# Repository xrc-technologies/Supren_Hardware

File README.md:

# Supren_Hardware
Hardware for Supren Radio Controller

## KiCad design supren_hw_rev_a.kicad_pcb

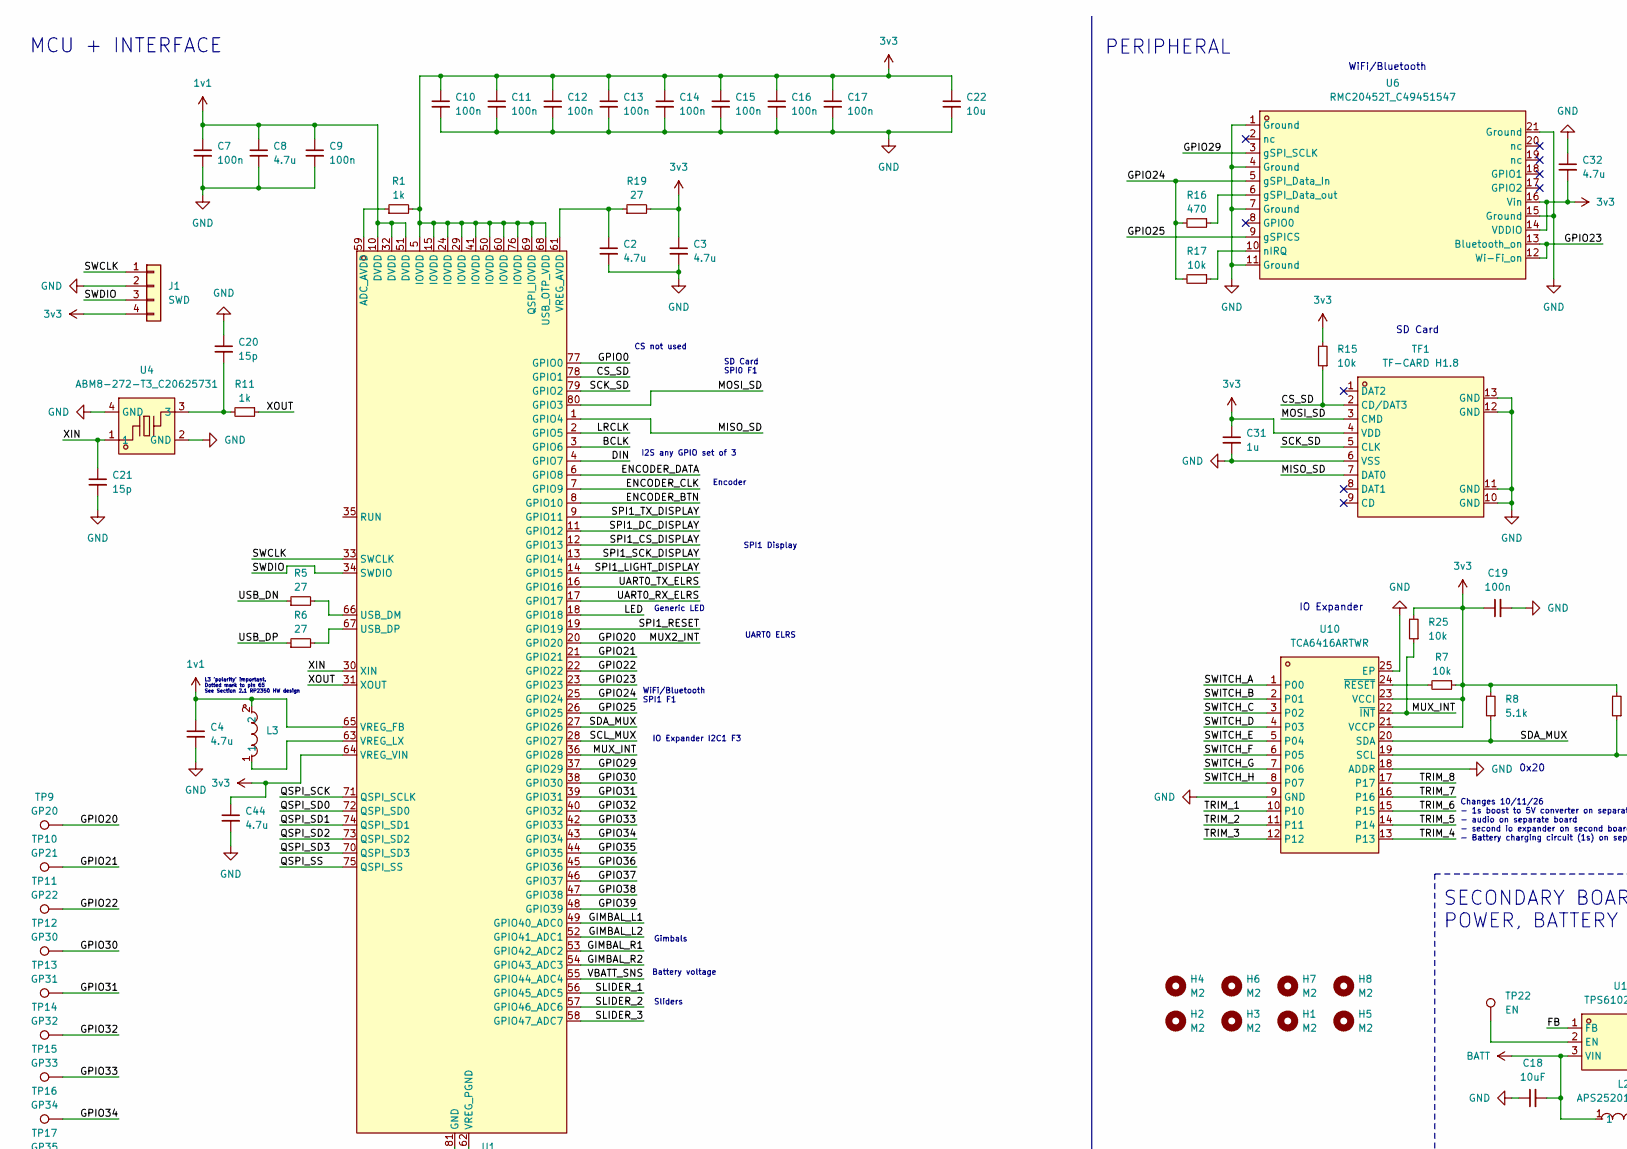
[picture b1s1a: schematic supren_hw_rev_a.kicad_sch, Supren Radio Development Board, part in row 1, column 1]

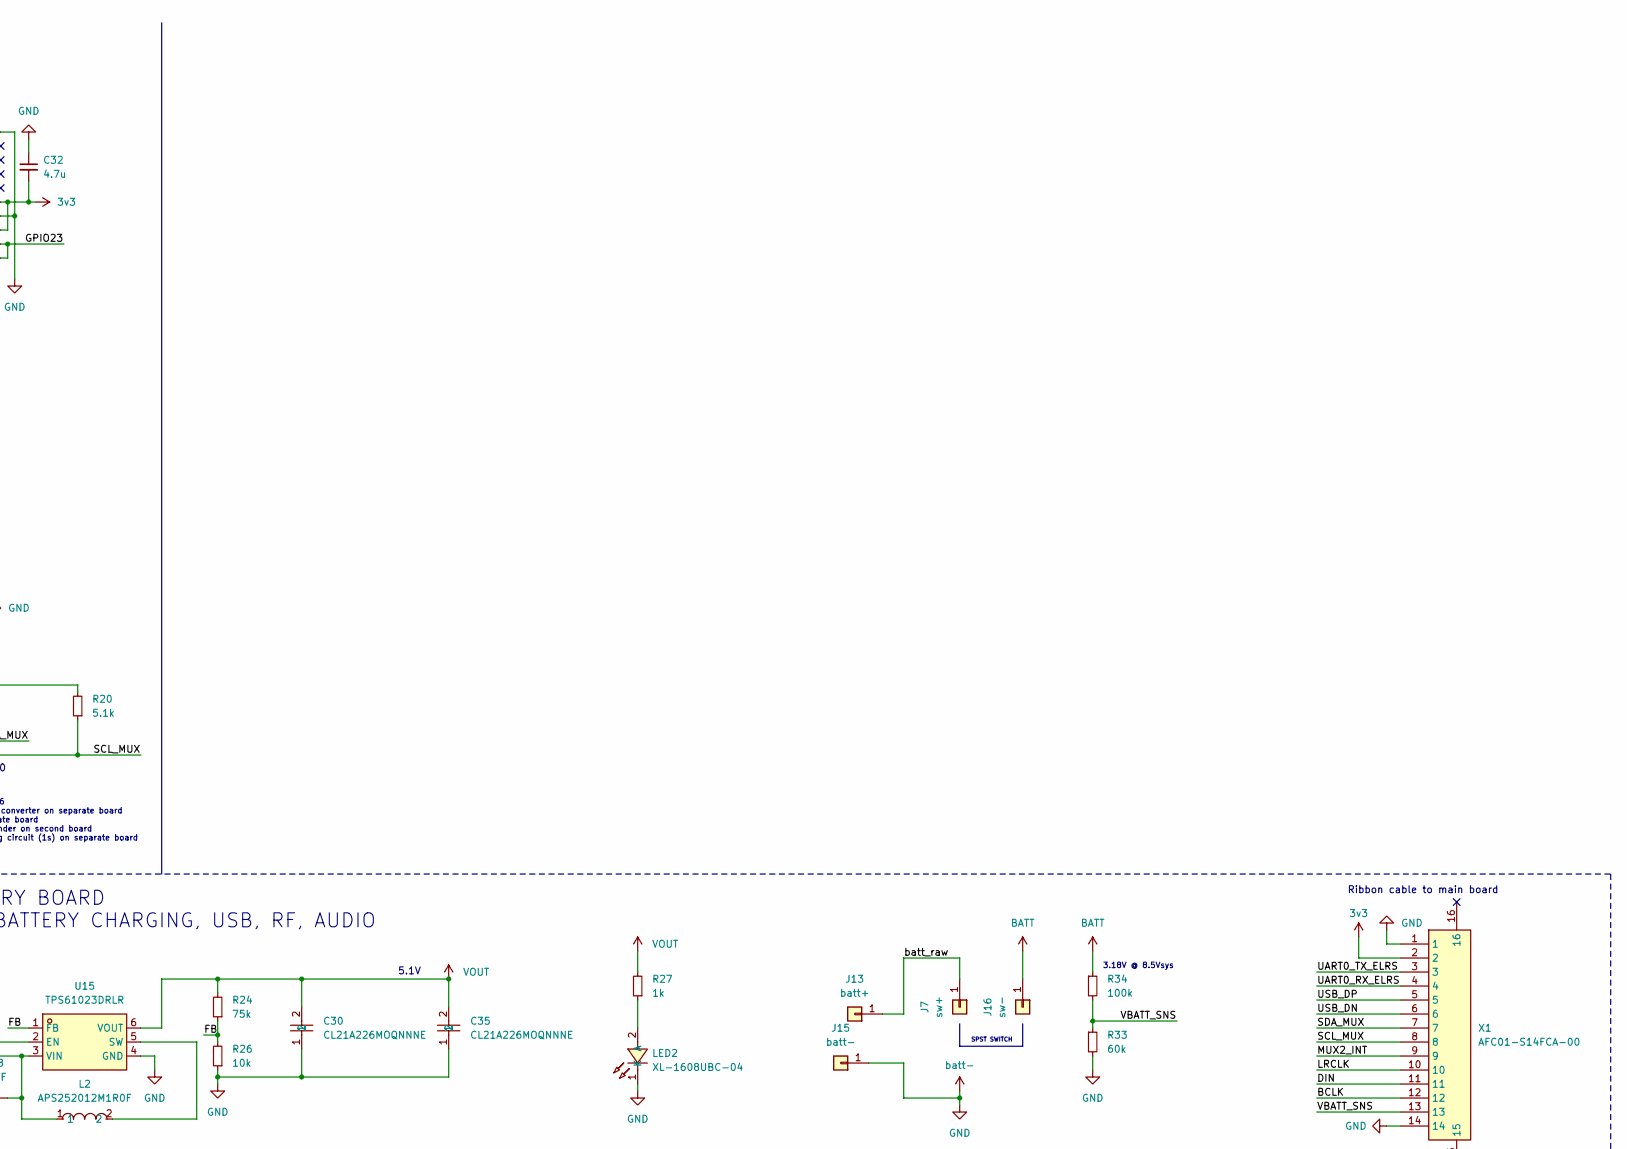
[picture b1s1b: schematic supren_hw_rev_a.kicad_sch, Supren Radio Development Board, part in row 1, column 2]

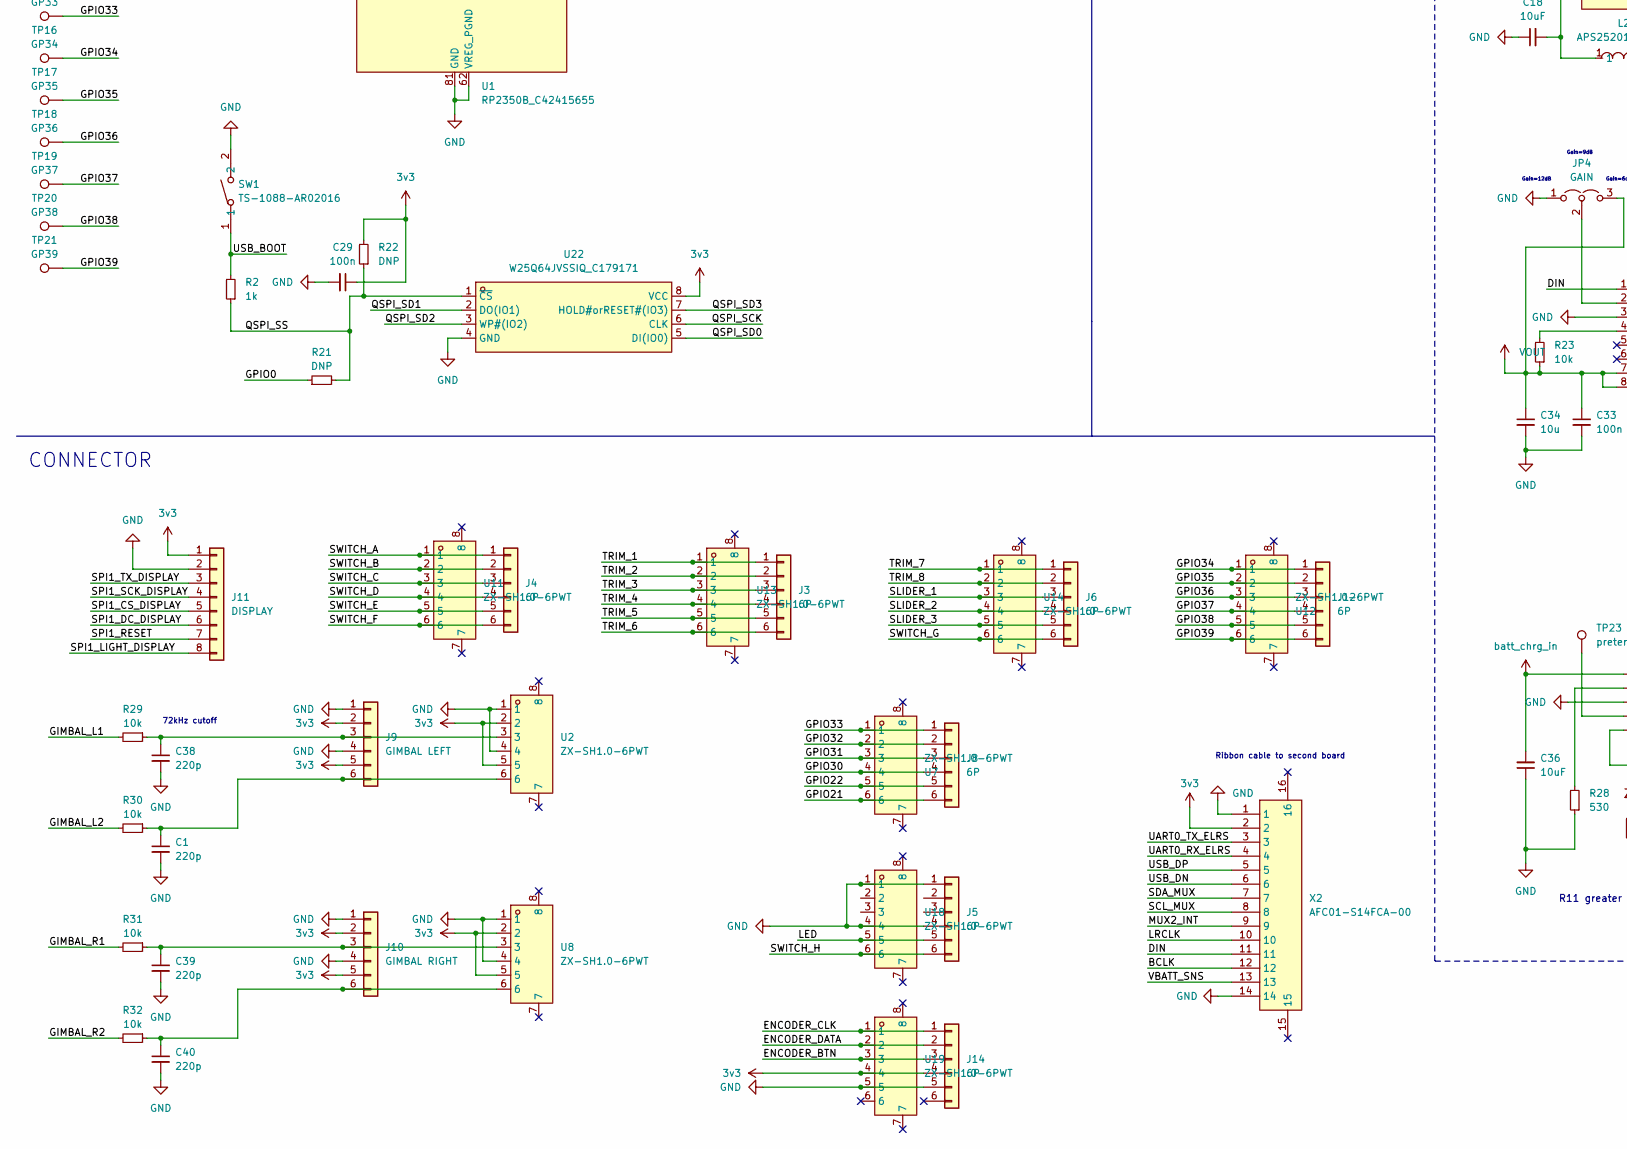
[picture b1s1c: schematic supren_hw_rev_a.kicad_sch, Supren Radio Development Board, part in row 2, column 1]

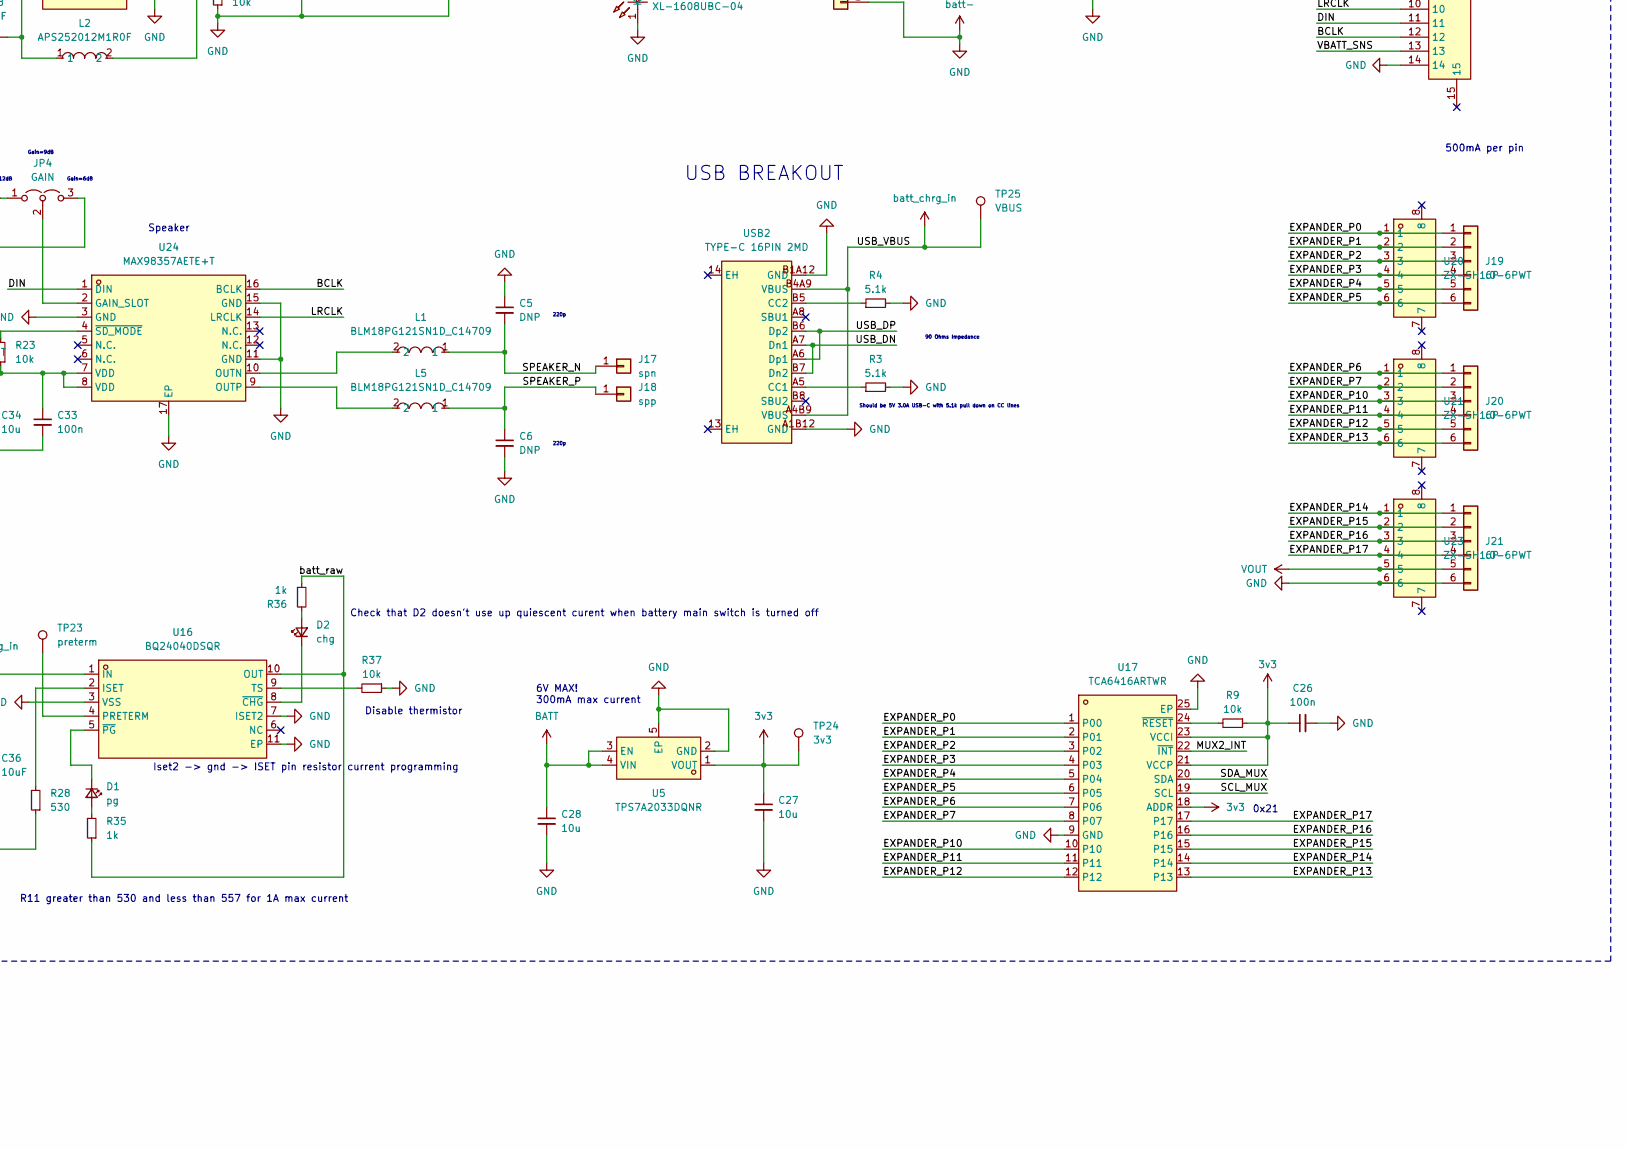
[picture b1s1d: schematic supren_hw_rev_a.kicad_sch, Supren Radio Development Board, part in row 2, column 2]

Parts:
C1, C38, C39, C40: 220p; C_0402_1005Metric
C2, C3, C4, C8, C32, C44: 4.7u; C_0603_1608Metric
C5, C6: DNP; C_0402_1005Metric
C7, C9, C10, C11, C12, C13, C14, C15, C16, C17, C19, C26, C29, C33: 100n; C_0402_1005Metric
C18: 10uF; C_0805_2012Metric; LCSC Part C14663
C20, C21: 15p; C_0402_1005Metric
C22, C27, C28, C34: 10u; C_0402_1005Metric
C30, C35: CL21A226MOQNNNE; C_0805_2012Metric; MPN CL21A226MOQNNNE; LCSC Part C98190
C31: 1u; C_0402_1005Metric
C36: 10uF; C_0805_2012Metric
D1: pg; LED_0603_1608Metric
D2: chg; LED_0603_1608Metric
H1, H2, H3, H4, H5, H6, H7, H8: M2; MountingHole_2.2mm_M2
J1: SWD; 4p_smd_small
J3: 6P; 6p_smd_small-3x2
J4, J5, J6, J8, J12, J14, J19, J20, J21: 6P; 6p_smd_small
J7: sw+; 1p_smd_small
J9: GIMBAL LEFT; 6p_smd_small
J10: GIMBAL RIGHT; 6p_smd_small
J11: DISPLAY; PinHeader_1x08_P2.54mm_Vertical-mod
J13: batt+; 1p_smd_small
J15: batt-; 1p_smd_small
J16: sw-; 1p_smd_small
J17: spn; 1p_smd_small
J18: spp; 1p_smd_small
JP4: GAIN; SolderJumper-3_P1.3mm_Open_Pad1.0x1.5mm
L1, L5: BLM18PG121SN1D_C14709; L0603; MPN BLM18PG121SN1D; LCSC Part C14709
L2: APS252012M1R0F; IND-SMD_L2.5-W2.0; MPN APS252012M1R0F; LCSC Part C47327422
L3: AOTA-B201610S3R3-101-T; IND-SMD_L2.0-W1.6_AOTA-B201610S3R3-101-T; MPN AOTA-B201610S3R3-101-T; LCSC Part C42411119
LED2: XL-1608UBC-04; LED0603-RD_BLUE; LCSC Part C965807
R1, R2, R11, R27, R35, R36: 1k; R_0402_1005Metric
R3, R4, R8, R20: 5.1k; R_0402_1005Metric
R5, R6, R19: 27; R_0402_1005Metric
R7, R9, R15, R17, R23, R25, R26, R29, R30, R31, R32, R37: 10k; R_0402_1005Metric
R16: 470; R_0402_1005Metric
R21, R22: DNP; R_0402_1005Metric
R24: 75k; R_0402_1005Metric
R28: 530; R_0402_1005Metric
R33: 60k; R_0402_1005Metric
R34: 100k; R_0402_1005Metric
SW1: TS-1088-AR02016; SW-SMD_L3.9-W3.0-P4.45; LCSC Part C720477
TF1: TF-CARD H1.8; TF-SMD_TF-CARD-H1.8; MPN TF-CARD H1.8; LCSC Part C7529389
TP9: GP20; TestPoint_Pad_D1.0mm-mod
TP10: GP21; TestPoint_Pad_D1.0mm-mod
TP11: GP22; TestPoint_Pad_D1.0mm-mod
TP12: GP30; TestPoint_Pad_D1.0mm-mod
TP13: GP31; TestPoint_Pad_D1.0mm-mod
TP14: GP32; TestPoint_Pad_D1.0mm-mod
TP15: GP33; TestPoint_Pad_D1.0mm-mod
TP16: GP34; TestPoint_Pad_D1.0mm-mod
TP17: GP35; TestPoint_Pad_D1.0mm-mod
TP18: GP36; TestPoint_Pad_D1.0mm-mod
TP19: GP37; TestPoint_Pad_D1.0mm-mod
TP20: GP38; TestPoint_Pad_D1.0mm-mod
TP21: GP39; TestPoint_Pad_D1.0mm-mod
TP22: EN; TestPoint_Pad_1.0x1.0mm
TP23: preterm; TestPoint_Pad_1.0x1.0mm
TP24: 3v3; TestPoint_Pad_1.0x1.0mm
TP25: VBUS; TestPoint_Pad_1.0x1.0mm
U1: RP2350B_C42415655; QFN-80_L10.0-W10.0-P0.40-TL-EP3.4; MPN RP2350B; LCSC Part C42415655
U2, U7, U8, U11, U12, U13, U14, U18, U19, U20, U21, U23: ZX-SH1.0-6PWT; CONN-SMD_6P-P1.00_MEGASTAR_ZX-SH1.0-6PWT; MPN ZX-SH1.0-6PWT; LCSC Part C7430448
U4: ABM8-272-T3_C20625731; CRYSTAL-SMD_4P-L3.2-W2.5-BL; LCSC Part C20625731
U5: TPS7A2033DQNR; UDFN-4_L1.0-W1.0-P0.65-TL; MPN TPS7A2033DQNR; LCSC Part C46459900
U6: RMC20452T_C49451547; WIRELM-SMD_RMC20452T; MPN RMC20452T; LCSC Part C49451547
U10, U17: TCA6416ARTWR; WQFN-24_L4.0-W4.0-P0.50-TL-EP2.5; MPN TCA6416ARTWR; LCSC Part C182336
U15: TPS61023DRLR; SOT-563_L1.6-W1.2-P0.50-LS1.6-BR; MPN TPS61023DRLR; LCSC Part C919459
U16: BQ24040DSQR; WSON-10_L2.0-W2.0-P0.40-BL-EP; MPN BQ24040DSQR; LCSC Part C81080
U22: W25Q64JVSSIQ_C179171; SOIC-8_L5.3-W5.3-P1.27-LS8.0-BL; MPN W25Q64JVSSIQ; LCSC Part C179171
U24: MAX98357AETE+T; TQFN-16_L3.0-W3.0-P0.50-BL-EP1.5; MPN MAX98357AETE+T; LCSC Part C910544
USB2: TYPE-C 16PIN 2MD; USB-C-SMD_TYPE-C-16PIN-2MD-073; MPN TYPE-C 16PIN 2MD(073); LCSC Part C2765186
X1, X2: AFC01-S14FCA-00; FPC-SMD_AFC01-S14FCA-00; MPN AFC01-S14FCA-00; LCSC Part C262663

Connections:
1v1: C4.1, C7.1, C8.1, C9.1, L3.2, U1.10 (DVDD), U1.32 (DVDD), U1.51 (DVDD), U1.65 (VREG_FB)
3v3: C3.1, C10.1, C11.1, C12.1, C13.1, C14.1, C15.1, C16.1, C17.1, C19.1, C22.1, C26.1, C27.1, C29.1, C31.1, C32.2, C44.1, J1.4, J9.2, J9.5, J10.2, J10.5, J11.1, J14.4, R1.2, R7.1, R8.2, R9.1, R15.2, R19.2, R20.2, R22.2, R25.2, TF1.4 (VDD), TP24.1 (1_1), U1.5 (IOVDD), U1.15 (IOVDD), U1.24 (IOVDD), U1.29 (IOVDD), U1.41 (IOVDD), U1.50 (IOVDD), U1.60 (IOVDD), U1.64 (VREG_VIN), U1.68 (USB_OTP_VDD), U1.69 (QSPI_IOVDD), U1.76 (IOVDD), U2.2, U2.5, U5.1 (VOUT), U6.14 (VDDIO), U6.16 (Vin), U8.2, U8.5, U10.21 (VCCP), U10.23 (VCCI), U17.18 (ADDR), U17.21 (VCCP), U17.23 (VCCI), U19.4, U22.8 (VCC), X1.2, X2.2
/BCLK: U1.3 (GPIO6), U24.16 (BCLK), X1.12, X2.12
/CS_SD: R15.1, TF1.2 (CD/DAT3), U1.78 (GPIO1)
/DIN: U1.4 (GPIO7), U24.1 (DIN), X1.11, X2.11
/ENCODER_BTN: J14.3, U1.8 (GPIO10), U19.3
/ENCODER_CLK: J14.1, U1.7 (GPIO9), U19.1
/ENCODER_DATA: J14.2, U1.6 (GPIO8), U19.2
/EXPANDER_P0: J19.1, U17.1 (P00), U20.1
/EXPANDER_P1: J19.2, U17.2 (P01), U20.2
/EXPANDER_P2: J19.3, U17.3 (P02), U20.3
/EXPANDER_P3: J19.4, U17.4 (P03), U20.4
/EXPANDER_P4: J19.5, U17.5 (P04), U20.5
/EXPANDER_P5: J19.6, U17.6 (P05), U20.6
/EXPANDER_P6: J20.1, U17.7 (P06), U21.1
/EXPANDER_P7: J20.2, U17.8 (P07), U21.2
/EXPANDER_P10: J20.3, U17.10, U21.3
/EXPANDER_P11: J20.4, U17.11, U21.4
/EXPANDER_P12: J20.5, U17.12, U21.5
/EXPANDER_P13: J20.6, U17.13, U21.6
/EXPANDER_P14: J21.1, U17.14, U23.1
/EXPANDER_P15: J21.2, U17.15, U23.2
/EXPANDER_P16: J21.3, U17.16, U23.3
/EXPANDER_P17: J21.4, U17.17, U23.4
/FB: R24.1, R26.2, U15.1 (FB)
/GIMBAL_L1: R29.2, U1.49 (GPIO40_ADC0)
/GIMBAL_L2: R30.2, U1.52 (GPIO41_ADC1)
/GIMBAL_R1: R31.2, U1.53 (GPIO42_ADC2)
/GIMBAL_R2: R32.2, U1.54 (GPIO43_ADC3)
/GPIO0: R21.1, U1.77 (GPIO0)
/GPIO20: TP9.1 (1_1), U1.20 (GPIO20), U17.22 (~INT), X1.9, X2.9
/GPIO21: J8.6, TP10.1 (1_1), U1.21 (GPIO21), U7.6
/GPIO22: J8.5, TP11.1 (1_1), U1.22 (GPIO22), U7.5
/GPIO23: U1.23 (GPIO23), U6.12 (Wi-Fi_on), U6.13 (Bluetooth_on)
/GPIO24: R16.2, R17.2, U1.25 (GPIO24), U6.5 (gSPI_Data_In)
/GPIO25: U1.26 (GPIO25), U6.9 (gSPICS)
/GPIO29: U1.37 (GPIO29), U6.3 (gSPI_SCLK)
/GPIO30: J8.4, TP12.1 (1_1), U1.38 (GPIO30), U7.4
/GPIO31: J8.3, TP13.1 (1_1), U1.39 (GPIO31), U7.3
/GPIO32: J8.2, TP14.1 (1_1), U1.40 (GPIO32), U7.2
/GPIO33: J8.1, TP15.1 (1_1), U1.42 (GPIO33), U7.1
/GPIO34: J12.1, TP16.1 (1_1), U1.43 (GPIO34), U12.1
/GPIO35: J12.2, TP17.1 (1_1), U1.44 (GPIO35), U12.2
/GPIO36: J12.3, TP18.1 (1_1), U1.45 (GPIO36), U12.3
/GPIO37: J12.4, TP19.1 (1_1), U1.46 (GPIO37), U12.4
/GPIO38: J12.5, TP20.1 (1_1), U1.47 (GPIO38), U12.5
/GPIO39: J12.6, TP21.1 (1_1), U1.48 (GPIO39), U12.6
/LED: J5.5, U1.18 (GPIO18), U18.5
/LRCLK: U1.2 (GPIO5), U24.14 (LRCLK), X1.10, X2.10
/MISO_SD: TF1.7 (DAT0), U1.1 (GPIO4)
/MOSI_SD: TF1.3 (CMD), U1.80 (GPIO3)
/MUX_INT: R25.1, U1.36 (GPIO28), U10.22 (~INT)
/QSPI_SCK: U1.71 (QSPI_SCLK), U22.6 (CLK)
/QSPI_SD0: U1.72 (QSPI_SD0), U22.5 (DI(IO0))
/QSPI_SD1: U1.74 (QSPI_SD1), U22.2 (DO(IO1))
/QSPI_SD2: U1.73 (QSPI_SD2), U22.3 (WP#(IO2))
/QSPI_SD3: U1.70 (QSPI_SD3), U22.7 (HOLD#orRESET#(IO3))
/QSPI_SS: R2.1, R21.2, R22.1, U1.75 (QSPI_SS), U22.1 (~CS)
/SCK_SD: TF1.5 (CLK), U1.79 (GPIO2)
/SCL_MUX: R20.1, U1.28 (GPIO27), U10.19 (SCL), U17.19 (SCL), X1.8, X2.8
/SDA_MUX: R8.1, U1.27 (GPIO26), U10.20 (SDA), U17.20 (SDA), X1.7, X2.7
/SLIDER_1: J6.3, U1.56 (GPIO45_ADC5), U14.3
/SLIDER_2: J6.4, U1.57 (GPIO46_ADC6), U14.4
/SLIDER_3: J6.5, U1.58 (GPIO47_ADC7), U14.5
/SPEAKER_N: C5.2, J17.1 (Pin_1_1), L1.1
/SPEAKER_P: C6.1, J18.1 (Pin_1_1), L5.1
/SPI1_CS_DISPLAY: J11.5, U1.12 (GPIO13)
/SPI1_DC_DISPLAY: J11.6, U1.11 (GPIO12)
/SPI1_LIGHT_DISPLAY: J11.8, U1.14 (GPIO15)
/SPI1_RESET: J11.7, U1.19 (GPIO19)
/SPI1_SCK_DISPLAY: J11.4, U1.13 (GPIO14)
/SPI1_TX_DISPLAY: J11.3, U1.9 (GPIO11)
/SWCLK: J1.1, U1.33 (SWCLK)
/SWDIO: J1.3, U1.34 (SWDIO)
/SWITCH_A: J4.1, U10.1 (P00), U11.1
/SWITCH_B: J4.2, U10.2 (P01), U11.2
/SWITCH_C: J4.3, U10.3 (P02), U11.3
/SWITCH_D: J4.4, U10.4 (P03), U11.4
/SWITCH_E: J4.5, U10.5 (P04), U11.5
/SWITCH_F: J4.6, U10.6 (P05), U11.6
/SWITCH_G: J6.6, U10.7 (P06), U14.6
/SWITCH_H: J5.6, U10.8 (P07), U18.6
/TRIM_1: J3.1, U10.10, U13.1
/TRIM_2: J3.2, U10.11, U13.2
/TRIM_3: J3.3, U10.12, U13.3
/TRIM_4: J3.4, U10.13, U13.4
/TRIM_5: J3.5, U10.14, U13.5
/TRIM_6: J3.6, U10.15, U13.6
/TRIM_7: J6.1, U10.16, U14.1
/TRIM_8: J6.2, U10.17, U14.2
/UART0_RX_ELRS: U1.17 (GPIO17), X1.4, X2.4
/UART0_TX_ELRS: U1.16 (GPIO16), X1.3, X2.3
/USB_BOOT: R2.2, SW1.1
/USB_DN: R5.1, USB2.A7 (Dn1), USB2.B7 (Dn2), X1.6, X2.6
/USB_DP: R6.1, USB2.A6 (Dp1), USB2.B6 (Dp2), X1.5, X2.5
/VBATT_SNS: R33.1, R34.2, U1.55 (GPIO44_ADC4), X1.13, X2.13
/XIN: C21.1, U1.30 (XIN), U4.1
/XOUT: R11.1, U1.31 (XOUT)
/batt_raw: J7.1 (Pin_1_1), J13.1 (Pin_1_1), R35.1, R36.1, U16.10 (OUT)
BATT: C18.2, C28.1, J16.1 (Pin_1_1), L2.1, R34.1, U5.3 (EN), U5.4 (VIN), U15.3 (VIN)
GND: C1.2, C2.2, C3.2, C4.2, C5.1, C6.2, C7.2, C8.2, C9.2, C10.2, C11.2, C12.2, C13.2, C14.2, C15.2, C16.2, C17.2, C18.1, C19.2, C20.1, C21.2, C22.2, C26.2, C27.2, C28.2, C29.2, C30.1, C31.2, C32.1, C33.2, C34.2, C35.1, C36.1, C38.2, C39.2, C40.2, C44.2, J1.2, J5.1, J5.4, J9.1, J9.4, J10.1, J10.4, J11.2, J14.5, J15.1 (Pin_1_1), J21.6, JP4.1 (A), LED2.1 (K), R3.2, R4.2, R26.1, R28.1, R33.2, R37.1, SW1.2, TF1.6 (VSS), TF1.10 (GND), TF1.11 (GND), TF1.12 (GND), TF1.13 (GND), U1.62 (VREG_PGND), U1.81 (GND), U2.1, U2.4, U4.2 (GND), U4.4 (GND), U5.2 (GND), U5.5 (EP), U6.1 (Ground), U6.4 (Ground), U6.7 (Ground), U6.11 (Ground), U6.15 (Ground), U6.21 (Ground), U8.1, U8.4, U10.9 (GND), U10.18 (ADDR), U10.25 (EP), U15.4 (GND), U16.3 (VSS), U16.7 (ISET2), U16.11 (EP), U17.9 (GND), U17.25 (EP), U18.1, U18.4, U19.5, U22.4 (GND), U23.6, U24.3 (GND), U24.11 (GND), U24.15 (GND), U24.17 (EP), USB2.A1B12 (GND), USB2.B1A12 (GND), X1.1, X1.14, X2.1, X2.14
unnamed: C20.2, R11.2, U4.3
unnamed: D1.2 (A), R35.2
unnamed: D1.1 (K), U16.5 (~PG)
unnamed: D2.2 (A), R36.2
unnamed: D2.1 (K), U16.8 (~CHG)
unnamed: C38.1, J9.3, R29.1, U2.3
unnamed: C1.1, J9.6, R30.1, U2.6
unnamed: C39.1, J10.3, R31.1, U8.3
unnamed: C40.1, J10.6, R32.1, U8.6
unnamed: JP4.2 (C), U24.2 (GAIN_SLOT)
unnamed: LED2.2 (A), R27.1
unnamed: R1.1, U1.59 (ADC_AVDD)
unnamed: R5.2, U1.66 (USB_DM)
unnamed: R6.2, U1.67 (USB_DP)
unnamed: C2.1, R19.1, U1.61 (VREG_AVDD)
unnamed: L3.1, U1.63 (VREG_LX)
unnamed: R16.1, U6.6 (gSPI_Data_out)
unnamed: R17.1, U6.10 (nIRQ)
unnamed: R7.2, U10.24 (~RESET)
unnamed: TP22.1 (1_1), U15.2 (EN)
unnamed: L2.2, U15.5 (SW)
unnamed: R28.2, U16.2 (ISET)
unnamed: TP23.1 (1_1), U16.4 (PRETERM)
unnamed: R37.2, U16.9 (TS)
unnamed: R9.2, U17.24 (~RESET)
unnamed: L1.2, U24.10 (OUTN)
unnamed: L5.2, U24.9 (OUTP)
unnamed: R23.2, U24.4 (~SD_MODE)
unnamed: R3.1, USB2.A5 (CC1)
unnamed: R4.1, USB2.B5 (CC2)
VOUT: C30.2, C33.1, C34.1, C35.2, J21.5, JP4.3 (B), R23.1, R24.2, R27.2, U15.6 (VOUT), U23.5, U24.7 (VDD), U24.8 (VDD)
batt_chrg_in: C36.2, TP25.1 (1_1), U16.1 (IN), USB2.A4B9 (VBUS), USB2.B4A9 (VBUS)

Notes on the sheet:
Sliders
CS not used
MCU + INTERFACE
SD Card SPI0 F1
R11 greater than 530 and less than 557 for 1A max current
I2S any GPIO set of 3
Gimbals
SPST SWITCH
220p
WiFi/Bluetooth SPI1 F1
6V MAX! 300mA max current
UART0 ELRS
IO Expander
CONNECTOR
0x20
WiFi/Bluetooth
0x21
Disable thermistor
PERIPHERAL
Ribbon cable to main board
Encoder
Ribbon cable to second board
IO Expander I2C1 F3
Generic LED
SD Card
Speaker
Check that D2 doesn't use up quiescent curent when battery main switch is turned off
500mA per pin
Gain=6dB
SPI1 Display
Battery voltage
Gain=9dB
Gain=12dB
L3 'polarity' important. Dotted mark to pin 65 See Section 2.1 RP2350 HW design
5.1V
SECONDARY BOARD POWER, BATTERY CHARGING, USB, RF, AUDIO
Iset2 -> gnd -> ISET pin resistor current programming
72kHz cutoff
Should be 5V 3.0A USB-C with 5.1k pull down on CC lines
90 Ohms Impedance

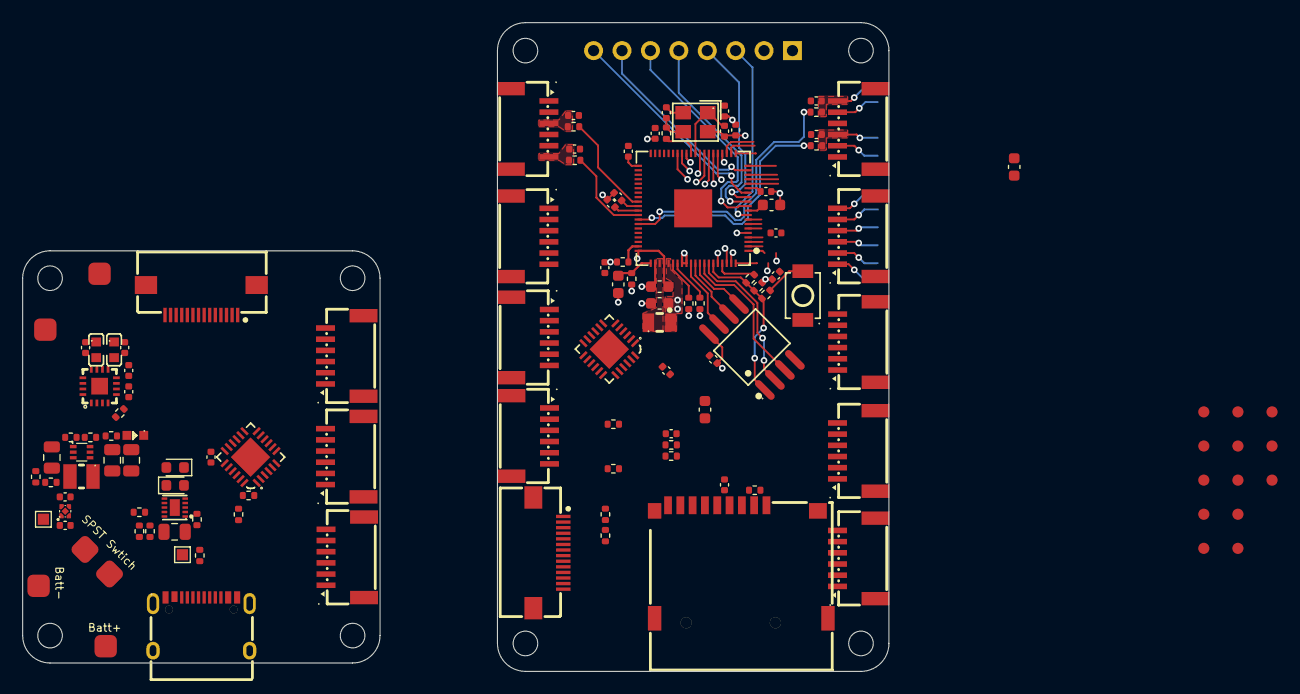
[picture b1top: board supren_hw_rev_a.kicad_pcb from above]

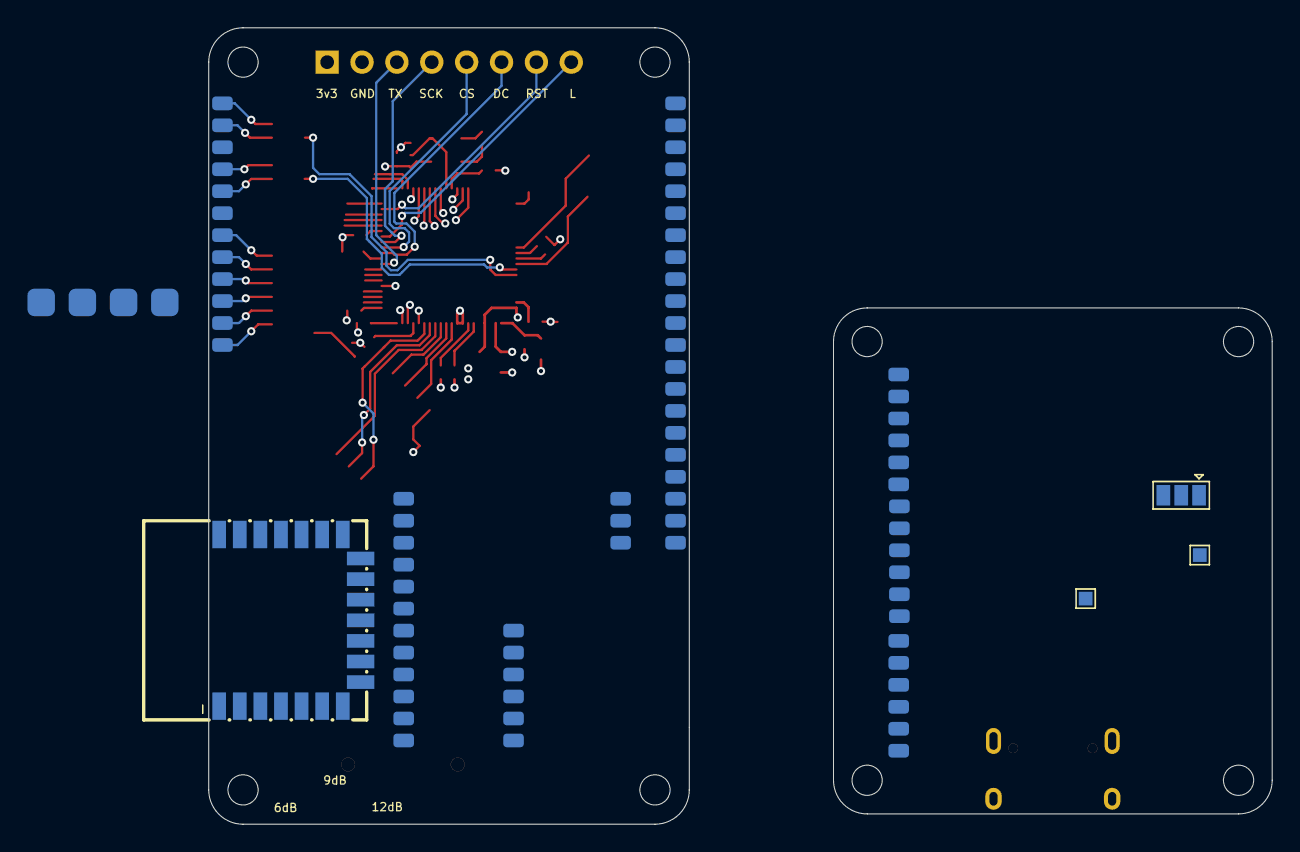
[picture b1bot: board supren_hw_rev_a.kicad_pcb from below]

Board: 6 copper layers, 77.5 x 58.0 mm, 149 parts (17 on the bottom side), 133 nets.

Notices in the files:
_restore_backup_2026-10-11T15-11-54-315/supren_hw_rev_a.kicad_sch:
CC BY-NC 4.0
